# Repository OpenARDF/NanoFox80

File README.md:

# NanoFox80
NanoFox80 is a (relatively) simple full-featured low-power 80m transmitter for use in foxoring competitions.

<b>KiCad</b>

The KiCad folder holds files for generating the schematic, BOM, and PCB files using KiCad. 

<b>Software</b>

The Software folder holds files for compiling executable code on Atmel Studio 7.

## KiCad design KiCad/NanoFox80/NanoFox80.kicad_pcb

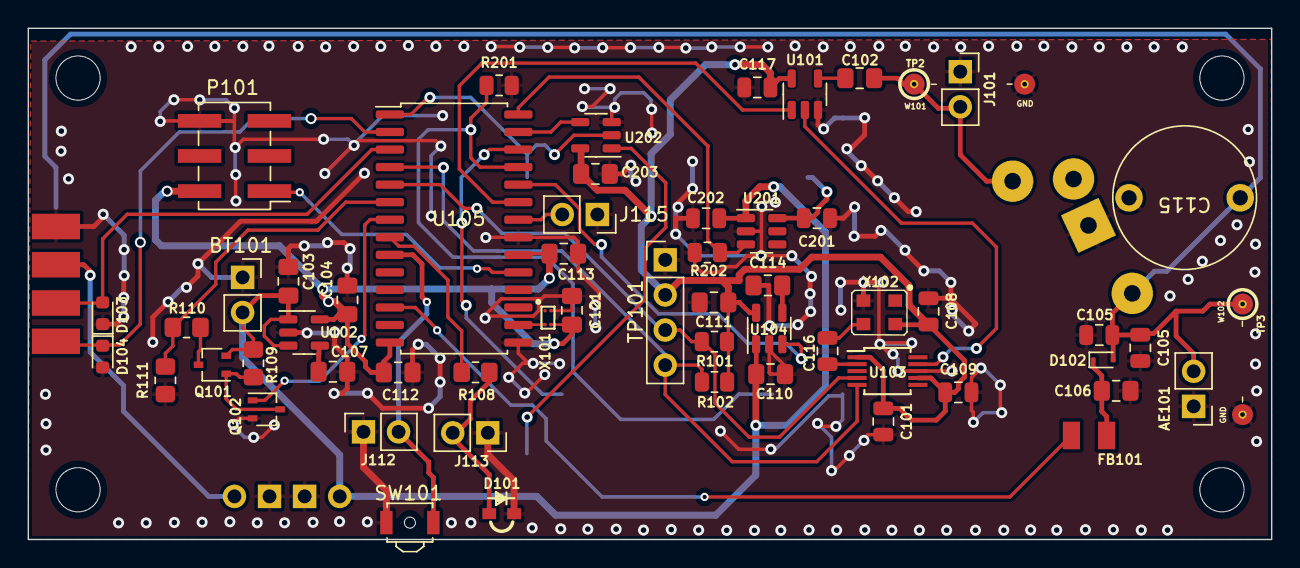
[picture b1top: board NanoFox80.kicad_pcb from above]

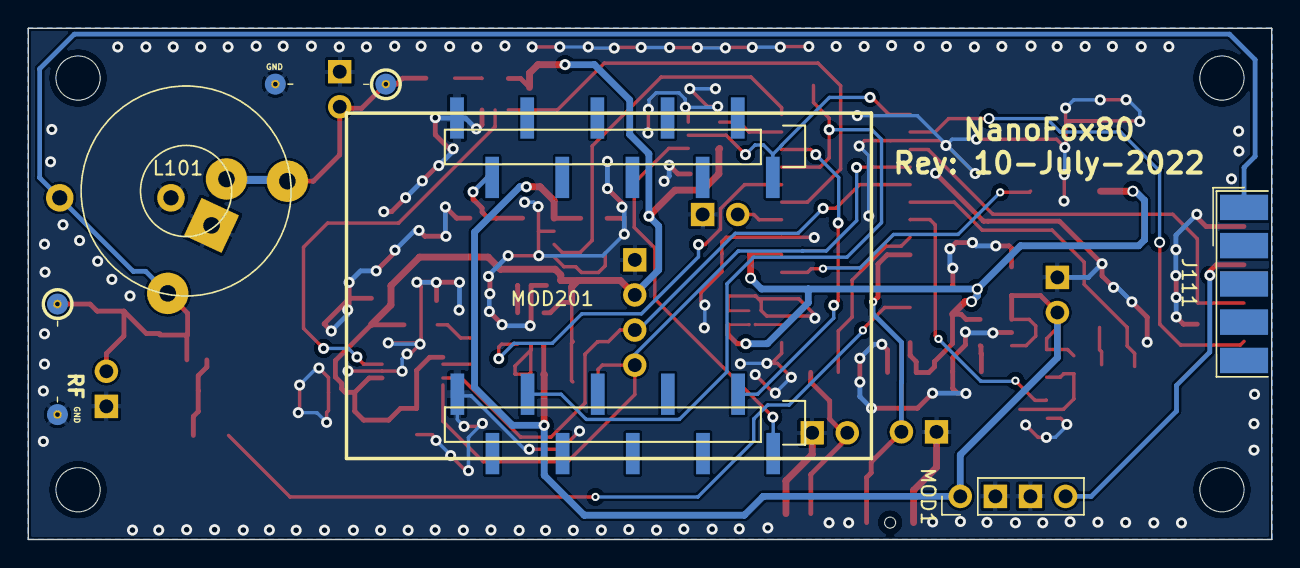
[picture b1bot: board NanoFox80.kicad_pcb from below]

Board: 2 copper layers, 90.0 x 37.0 mm, 61 parts (4 on the bottom side), 38 nets.

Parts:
AE101: Antenna_Shield; PinHeader_1x02_P2.54mm_Vertical
BT101: 3.5-9V; PinSocket_1x02_P2.54mm_Vertical
C101, C109: 470nF; C_0805_2012Metric
C102, C121, C203: 100nF; C_0805_2012Metric_Pad1.18x1.45mm_HandSolder
C103, C104, C110, C111: 10uF; C_0805_2012Metric_Pad1.18x1.45mm_HandSolder
C105, C105#2: 220pF; C_0805_2012Metric
C106, C112, C113: 470nF; C_0805_2012Metric_Pad1.18x1.45mm_HandSolder
C107, C114: 10nF; C_0805_2012Metric_Pad1.18x1.45mm_HandSolder
C108, C116, C117: 100nF; C_0805_2012Metric
C115: 15-60pF; CP_Radial_Ceramic_Trimmer_D9.4mm_P8.00mm
C201: 10uF; C_0805_2012Metric
C202: 4.7uF; C_0805_2012Metric
D101: LED_Filled; LED_APDA1806SECK
D102: SMV1253-079LF; D_SC-80
D103, D104: ESD9B5.0ST5G_1; D_0603_1608Metric
FB101: FerriteBead_Small; Ferrite_Bead_NFZ32BW881_Reflow
J101, J112, J113, J115: Conn_01x02; PinSocket_1x02_P2.54mm_Vertical
J111: DB9 Female; DSUB-9_Female_EdgeMount_P2.77mm
L101: 8uH; Autotransformer_Toroid_1Tap_Horizontal_D14.0mm_Amidon-T50
MOD1: AdaFruit Charger; PinHeader_1x04_P2.54mm_Vertical
MOD201: HUZZAH_ESP8266_Breakout; Adafruit_HUZZAH_ESP8266_Breakout_SM
P101: ISP/PDI; PinHeader_2x03_P2.54mm_Vertical_SMD
Q101: BSS84W-7-F; SOT-323_SC-70
Q102: BSS138W-7-F; SOT-323_SC-70
R101, R102, R202: 10k; R_0805_2012Metric
R108: 1k; R_0805_2012Metric_Pad1.20x1.40mm_HandSolder
R109: 100k; R_0805_2012Metric_Pad1.20x1.40mm_HandSolder
R110: 162k; R_0805_2012Metric_Pad1.20x1.40mm_HandSolder
R111: 12.4k; R_0805_2012Metric_Pad1.20x1.40mm_HandSolder
R201: 560k; R_0805_2012Metric
SW101: SW_SPST; SW_SPST_B3U-3000P-B
TP101: I2C1; PinHeader_1x04_P2.54mm_Vertical
U101: MC74VHC1G125; TSOT-23-5
U102, U104: LP2985-3.3; SOT-23-5
U103: SI5351; MSOP-10_3x3mm_P0.5mm
U105: AVR128DA28; SOIC-28W_7.5x17.9mm_P1.27mm
U201: TPS22810DBVT; SOT-23-6
U202: 74HC1G08; SOT-23-5
W101: TP2; Measurement_Point_ScopeProbe_Round-SMD-2sides-Pad_Small
W102: TP3; Measurement_Point_ScopeProbe_Round-SMD-2sides-Pad_Small
X101: SIT1566AC TCO; Oscillator_SMD_SiTime_SIT1566AC-4Pin_BGA
X102: 25 MHz; Crystal_SMD_TXETCLSANF-4Pin

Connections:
+3V3: C104.2, C112.1, C113.2, C121.2, P101.2, U102.5 (VOUT), U105.14 (AVDD), U105.20 (VDD), X101.3 (Vdd)
+BATT: BT101.2 (+), C103.2, C110.2, C202.2, MOD1.1, Q101.2 (S), R109.1, U102.1 (VIN), U102.3 (ON/~OFF), U104.1 (VIN), U201.1 (VIN)
Antenna: AE101.2 (A), C105.1, C105#2.1, C115.1, D102.2 (A), J111.1, L101.1, W102.1
Enable_RF: U104.3 (ON/~OFF), U105.24 (PA2)
Enable_Vdiv: Q102.1 (G), U105.7 (PD1)
GND: AE101.1 (Shield), BT101.1 (-), C101.2, C103.1, C104.1, C105.2, C105#2.2, C106.1, C107.2, C108.2, C109.2, C110.1, C111.1, C112.2, C113.1, C114.2, C115.2, C117.1, C121.1, C201.1, C202.1, C203.1, D101.1 (K), D103.1 (A1), D104.2 (A2), J101.1, J111.6, J112.1, J113.1, J115.1, L101.3, MOD1.2, MOD1.3, MOD201.10 (GND), MOD201.11 (GND), P101.6, Q102.2 (S), R111.1, R201.2, R202.1, SW101.2 (B), TP101.1, U101.3 (GND), U102.2 (GND), U103.8 (GND), U104.2 (GND), U105.15 (GND), U105.21 (GND), U201.2 (GND), U202.3 (GND), W101.2, W102.2, X101.4 (GND), X102.2 (GND)
unnamed: C102.1, J101.2, L101.2 (TAP), W101.1
unnamed: C102.2, U101.4 (Y)
unnamed: C106.2, D102.1 (K), FB101.1
unnamed: C107.1, U102.4 (BP)
unnamed: C114.1, U104.4 (BP)
unnamed: C116.1, U103.2 (XA)
unnamed: C116.2, X102.3 (OUT)
unnamed: C201.2, MOD201.9 (VBat), U201.6 (VOUT)
unnamed: D101.2 (A), J113.2, R108.2
unnamed: D103.2 (A2), J111.8, U105.3 (PC1/RxD1)
unnamed: D104.1 (A1), J111.9, U105.2 (PC0/TxD1)
unnamed: FB101.2, U105.12 (PD6/DAC)
unnamed: J112.2, SW101.1 (A), U105.9 (PD3)
unnamed: J115.2, U105.22 (PA0/EXTCLK)
unnamed: MOD201.20 (TX), U202.1
unnamed: P101.1, U105.19 (UDPI)
unnamed: Q101.1 (G), Q102.3 (D), R109.2
unnamed: Q101.3 (D), R110.2
unnamed: R101.2, TP101.3, U103.4 (SCL), U105.5 (PC3/SCL)
unnamed: R102.2, TP101.4, U103.5 (SDA), U105.4 (PC2/SDA)
unnamed: R108.1, U105.8 (PD2)
unnamed: U101.1 (~OE), U105.23 (PA1)
unnamed: U101.2 (A), U103.9 (CLK1)
unnamed: U105.16 (PF0/XTAL32k1), X101.2 (OUT)
V+_Charging: J111.7, MOD1.4
VCC: C101.1, C108.1, C109.1, C111.2, C117.2, C203.2, R101.1, R102.1, TP101.2, U101.5 (VCC), U103.1 (VDD), U103.7 (VDDO), U104.5 (VOUT), U202.5 (VCC), X102.4 (Vcc)
Vbat: R110.1, R111.2, U105.6 (PD0/AIN0)
WIFI_ENABLE: R202.2, U105.28 (PA6), U201.3 (EN/UVLO)
WIFI_RX: MOD201.19 (RX), U105.26 (PA4)
WIFI_TX: U105.27 (PA5), U202.4
WiFi Module Detect: MOD201.13 (3V), R201.1, U105.25 (PA3)
~WIFI_RESET: MOD201.1 (~RST), U105.1 (PA7), U202.2

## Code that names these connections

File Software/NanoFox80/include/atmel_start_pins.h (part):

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/**
 * \brief Set ENABLE_Vdiv input/sense configuration
 *
 * Enable/disable ENABLE_Vdiv digital input buffer and pin change interrupt,
 * select pin interrupt edge/level sensing mode
 *
 * \param[in] isc PORT_ISC_INTDISABLE_gc    = Iterrupt disabled but input buffer enabled
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}

/**
 * \brief Set PC0 pull mode
 *
 * Configure pin to pull up, down or disable pull mode, supported pull
 * modes are defined by device used
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}

/**
 * \brief Set PC0 data direction
 *
 * Select if the pin data direction is input, output or disabled.
 * If disabled state is not possible, this function throws an assert.
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}

/**
 * \brief Set PC0 input/sense configuration
 *
 * Enable/disable PC0 digital input buffer and pin change interrupt,
 * select pin interrupt edge/level sensing mode
 *
 * \param[in] isc PORT_ISC_INTDISABLE_gc    = Iterrupt disabled but input buffer enabled
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}

/**
 * \brief Set PC0 inverted mode
 *
 * Enable or disable inverted I/O on a pin
 *
 * \param[in] inverted true  = I/O on PC0 is inverted
 *                     false = I/O on PC0 is not inverted
 */
static inline void PC0_set_inverted(const bool inverted)
{
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}

/**
 * \brief Set PC0 level
 *
 * Sets output level on a pin
 *
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}

/**
 * \brief Toggle output level on PC0
 *
 * Toggle the pin level
 */
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}

/**
 * \brief Get level on PC0
 *
 * Reads the level on a pin
 */
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}

/**
 * \brief Set PC1 pull mode
 *
 * Configure pin to pull up, down or disable pull mode, supported pull
 * modes are defined by device used
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}

/**
 * \brief Set PC1 data direction
 *
 * Select if the pin data direction is input, output or disabled.
 * If disabled state is not possible, this function throws an assert.
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}

/**
 * \brief Set PC1 input/sense configuration
 *
 * Enable/disable PC1 digital input buffer and pin change interrupt,
 * select pin interrupt edge/level sensing mode
 *
 * \param[in] isc PORT_ISC_INTDISABLE_gc    = Iterrupt disabled but input buffer enabled
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}

/**
 * \brief Set PC1 inverted mode
 *
 * Enable or disable inverted I/O on a pin
 *
 * \param[in] inverted true  = I/O on PC1 is inverted
 *                     false = I/O on PC1 is not inverted
 */
static inline void PC1_set_inverted(const bool inverted)
{
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}

/**
 * \brief Set PC1 level
 *
 * Sets output level on a pin
 *
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}

/**
 * \brief Toggle output level on PC1
 *
 * Toggle the pin level
 */
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}

/**
 * \brief Get level on PC1
 *
 * Reads the level on a pin
 */
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}

/**
 * \brief Set PC2 pull mode
 *
 * Configure pin to pull up, down or disable pull mode, supported pull
 * modes are defined by device used
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}

/**
 * \brief Set PC2 data direction
 *
 * Select if the pin data direction is input, output or disabled.
 * If disabled state is not possible, this function throws an assert.
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}

/**
 * \brief Set PC2 input/sense configuration
 *
 * Enable/disable PC2 digital input buffer and pin change interrupt,
 * select pin interrupt edge/level sensing mode
 *
 * \param[in] isc PORT_ISC_INTDISABLE_gc    = Iterrupt disabled but input buffer enabled
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}

/**
 * \brief Set PC2 inverted mode
 *
 * Enable or disable inverted I/O on a pin
 *
 * \param[in] inverted true  = I/O on PC2 is inverted
 *                     false = I/O on PC2 is not inverted
 */
static inline void PC2_set_inverted(const bool inverted)
{
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}

/**
 * \brief Set PC2 level
 *
 * Sets output level on a pin
 *
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}

/**
 * \brief Toggle output level on PC2
 *
 * Toggle the pin level
 */
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}

/**
 * \brief Get level on PC2
 *
 * Reads the level on a pin
 */
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}

/**
 * \brief Set PC3 pull mode
 *
 * Configure pin to pull up, down or disable pull mode, supported pull
 * modes are defined by device used
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}

/**
 * \brief Set PC3 data direction
 *
 * Select if the pin data direction is input, output or disabled.
 * If disabled state is not possible, this function throws an assert.
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}

/**
 * \brief Set PC3 input/sense configuration
 *
 * Enable/disable PC3 digital input buffer and pin change interrupt,
 * select pin interrupt edge/level sensing mode
 *
 * \param[in] isc PORT_ISC_INTDISABLE_gc    = Iterrupt disabled but input buffer enabled
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}

/**
 * \brief Set PC3 inverted mode
 *
 * Enable or disable inverted I/O on a pin
 *
 * \param[in] inverted true  = I/O on PC3 is inverted
 *                     false = I/O on PC3 is not inverted
 */
static inline void PC3_set_inverted(const bool inverted)
{
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}

/**
 * \brief Set PC3 level
 *
 * Sets output level on a pin
 *
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}

/**
 * \brief Toggle output level on PC3
 *
 * Toggle the pin level
 */
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}

/**
 * \brief Get level on PC3
 *
 * Reads the level on a pin
 */
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}

/**
 * \brief Set PD0 pull mode
 *
 * Configure pin to pull up, down or disable pull mode, supported pull
 * modes are defined by device used
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}

/**
 * \brief Set PD0 data direction
 *
 * Select if the pin data direction is input, output or disabled.
 * If disabled state is not possible, this function throws an assert.
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}

/**
 * \brief Set PD0 input/sense configuration
 *
 * Enable/disable PD0 digital input buffer and pin change interrupt,
 * select pin interrupt edge/level sensing mode
 *
 * \param[in] isc PORT_ISC_INTDISABLE_gc    = Iterrupt disabled but input buffer enabled
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}

/**
 * \brief Set PD0 inverted mode
 *
 * Enable or disable inverted I/O on a pin
 *
 * \param[in] inverted true  = I/O on PD0 is inverted
 *                     false = I/O on PD0 is not inverted
 */
static inline void PD0_set_inverted(const bool inverted)
{
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}

/**
 * \brief Set PD0 level
 *
 * Sets output level on a pin
 *
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}

/**
 * \brief Toggle output level on PD0
 *
 * Toggle the pin level
 */
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}

/**
 * \brief Get level on PD0
 *
 * Reads the level on a pin
 */
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}

/**
 * \brief Set PD6 pull mode
 *
 * Configure pin to pull up, down or disable pull mode, supported pull
 * modes are defined by device used
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}

/**
 * \brief Set PD6 data direction
 *
 * Select if the pin data direction is input, output or disabled.
 * If disabled state is not possible, this function throws an assert.
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}

/**
 * \brief Set PD6 input/sense configuration
 *
 * Enable/disable PD6 digital input buffer and pin change interrupt,
 * select pin interrupt edge/level sensing mode
 *
 * \param[in] isc PORT_ISC_INTDISABLE_gc    = Iterrupt disabled but input buffer enabled
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}

/**
 * \brief Set PD6 inverted mode
 *
 * Enable or disable inverted I/O on a pin
 *
 * \param[in] inverted true  = I/O on PD6 is inverted
 *                     false = I/O on PD6 is not inverted
 */
static inline void PD6_set_inverted(const bool inverted)
{
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}

/**
 * \brief Set PD6 level
 *
 * Sets output level on a pin
 *
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}

/**
 * \brief Toggle output level on PD6
 *
 * Toggle the pin level
 */
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}

/**
 * \brief Get level on PD6
 *
 * Reads the level on a pin
 */
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
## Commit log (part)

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2022-04-22 First Commit
    Adds KiCad files
2022-04-22 Removed backup files
2022-04-23 Schematic Updates
    o Specified missing part parameters
    o Added Q101 & Q102, R110, R111, to support battery voltage monitoring
    o Added JP104 and JP105 to support swapping inputs to
2022-04-23 Cleanup
2022-04-25 Added test points
    Added photos in Docs folder
    Added test points
2022-04-26 Updates
    o More parts specified
    o First cut at a PCB
2022-04-26 Schematic Update
    o Added ESD diodes
2022-04-26 Parts Update
    Changed LED to be a right-angle device
2022-04-26 BOM
    o Fixed BOM script
    o Generated preliminary BOM
2022-04-27 Updated Schematic & PCB
    o Corrected varactor circuit
    o Added level translation to USART
    o Added mounting holes to PCB
2022-04-28 Schematic Update
    Updated L101 information
2022-04-30 PCB Routed
    o First cut at PCB board
    o Gerbers updated
2022-04-30 PCB Updates
    o Added better silkscreen to X101
    o More stitch vias
2022-05-01 PCB Updates
    o Added holes for scope probe ground clips
2022-05-01 PCB Update
    Updated X101 footprint silkscreen
2022-05-02 Schematic & PCB updates
    o Moved X101 connection to U105
    o Added header to pin 22 of U105
    o Updated schematic and PCB
    o Generated new Gerbers
2022-05-03 Updated Footprints
    o Corrected U106, U107 and U103 footprints
    o Updated Gerbers
2022-05-04 Schematic & PCB Updates
    o Fixed pinout of Q101
    o Changed device for U103
    o Corrected PCB for Q101 change
    o Updated PCB Rev
    o Updated BOM
2022-05-04 Schematic, BOM and PCB Updates
    o Changed parts spec'd for Q101 and Q102
    o Updated footprints
    o Updated PCB
    o Updated Gerbers
    o Updated BOM
2022-05-05 PCB Update
    o Corrected footprint for U103
    o Updated Gerbers
    o Updated BOM
2022-05-05 Moved Gerbers
    o Added a folder to hold all the Gerber files
2022-06-29 Last PLL Changes
    Merge last development changes supporting the PLL concept design
2022-06-29 Development for Si5351
    First changes for Si5351 design approach
2022-06-30 Development
    o Schematic updates for Si5351 approach
2022-06-30 Development
    o Addressed ERC errors
    o Added trimmer capacitor
    o Cosmetic changes to schematic
2022-06-30 Development
    o Added ESD diodes
    o Added WiFi support
2022-06-30 Development
    o Added last Microchip Studio files developed for the PLL design
2022-06-30 Development
    o Added Software folder
2022-07-01 Development
    o Set all footprints to approximate values
2022-07-01 Development
    Updated .gitignore
2022-07-02 Development
    o Added initial software folder
2022-07-02 Development
    o Removed zip files
2022-07-02 Development
    o Changes to footprints in schematic
2022-07-03 Development
    o Initialize PA7 correctly
2022-07-03 Development
    o Minor cleanup
2022-07-04 Development
    o Footprint edits
2022-07-04 Development
    o Tweak X102 footprint on PCB
2022-07-06 Development
    o Fixes to errors in schematic and PCB
2022-07-10 Development
    PCB changes
2022-07-10 Development
    Small PCB tweaks
2022-07-11 Development
    PCB silkscreen change
2022-07-12 PCB Dev
    o Removed copper fill keep out zone beneath X101
2022-07-12 Built Gerbers
    o Uploading built Gerber files
2022-07-12 PCB Development
    Tweaks to X101 footprint
2022-08-06 Development Merge
    o Merge of FlexFox software ported to NanoFox hardware. Little debugging has been done at this point.
2022-08-07 Development
    Debug of power to SI5351.
2022-08-07 Development
    o Implemented a DAC setting command for the serial bus.
    o Removed the power-setting command from the serial bus.
2022-08-08 Schematic Update
    o Updated L101 info
2022-08-08 Development
    o Timed events are now partly working
2022-08-09 Debug
    o Corrected a potential infinite loop if the TCXO hardware fails
2022-08-09 Development
    o Fixed some LED blink issues
2022-08-09 Development
    Changes to SLP
    Version 0.42
2022-08-09 Development
    o Added SLP functionality: SLP 0 disables sleep; SLP 1 re-enables sleep; SLP starts sleep if it isn't enabled
    o Fixes a bug that prevented ADC from working after returning from sleep
    o Ver 0.43
2022-08-09 Development
    o The sleep countdown is now reset to 2 minutes every time a serial port command is sent to NanoFox.
    o Ver 0.44
2022-08-09 Development
    o Improved sleep current drain. Now down to 336 uA.
    o Ver 0.45
2022-08-09 Schematic Updates
    o Corrected the device symbol for the microcontroller.
2022-08-10 Development
    o Fixes several problems that prevented the RTC from incrementing during sleep when using the internal 32 kHz clock.
2022-08-11 Development
    o Fix for Morse code timing that could send extra elements after sending the station ID
    o EEPROM variables added for future support of setting foxoring event information
2022-08-12 Development
    o Ver 0.50
    o Added non-volatile variables and commands to support "Event" concept and master/slave synchronization
2022-08-13 Ver 0.51
    o Added code to test the cloning concept. It should successfully set a slave's clock.
    o Added support for enunciating with Morse LED blinks
    o Removed Goertzel algorithm
2022-08-15 Development
    o Fixes an issue preventing time from getting sync'd during cloning process
    o Master will never transmit now
    o 1 short buttonpress should start an event
    o 2 short buttonpresses should stop an event
    o Ver 0.52
2022-08-15 Development
    o Ver 0.52
2022-08-15 Development
    Ver 0.52
2022-08-16 Development
    Ver 0.53
    o Fixes to cloning process
2022-08-16 Development
    Ver 0.54
    o Corrects a problem with Master/Slave sending \n instead of \r.
    o Addresses an issue that might have been corrupting g_foxoring_fox
2022-08-16 Development
    Prevents a slave from recognizing MAS P<cr> command for one minute following a successful cloning session.
2022-08-16 Ver 0.56
    o Removed echoing of characters during cloning.
2022-08-16 Ver 0.57
    Removed more extraneous character traffic during cloning.
2022-08-17 Ver 0.58
    o Sync debug
2022-08-17 Ver 0.59
    o Corrects an issue where master would send the start time in the CLK F message
2022-08-17 Development
    o Slave LED illuminates continuously while cloning is taking place.
    o Long keypress no longer sends "Master" or "Slave" after a mode transition.
2022-08-21 Ver 0.6
    o Added BAT serial command to display battery voltage and threshold setting.
    o Added a battery threshold setting that sets at what voltage the LED blinks "V" to indicate low battery. By default it is 3.8V.
    o Added a checksum for cloning data, and a master/slave message exchange to implement serial data error detection.
    o Code cleanup and general bug fixes.
2022-08-22 Ver 0.61
    o Redesign of EEPROM module. Guard variables added between settings variables.
    o Corrects some problems with event behavior following a sync
    o Corrects some problems with event behavior when going between master and slave mode or changing fox setting.
2022-08-23 KiCad
    o Schematic updates
2022-08-29 Ver 0.62
    o Adds support for RTC calibration using the CLK C nnnnn serial command.
    o Cleans up some EEPROM design elements
    o Minor bug fixes.
2022-09-01 Ver 0.63
    o Corrects a bug that could prevent the finish time from getting saved when the CLK S serial command was used to set the start time.
2022-11-21 +BATT Fix
    Schematic change
2022-11-21 Update NanoFox80.kicad_sch
    Schematic tweaks.
2022-11-21 Update NanoFox80.kicad_sch
    More tweaks
2022-11-21 Update NanoFox80.kicad_sch
    Schematic tweak - added cap across switch
2022-11-22 Schematic Tweaks
    Added missing diode
2022-11-22 Update NanoFox80.kicad_sch
    Schematic tweaks
2022-11-22 Schematic
    Upped version number
2022-11-23 Ver 0.64
    o Improved pushbutton debounce
2023-05-19 Fixed for EEPROM Corruption?
    Made changes to serial port logic to remove most junk characters.
    Set Port C Rx and Tx pins high during sleep.
    Disabled the linkbus, which isn't supported right now
2023-05-28 Development
    Adding support for all radio orienteering events formats
2023-05-30 Development Ver 0.71
    Numerous fixes to serial port operation.
2023-06-02 Serial Port Change
    o When device goes to sleep only two things will re-enable the serial port: 1) cycle power, 2) press button
    o Ver 0.72
2023-06-03 Bug Fix
    Resolves a bug that prevented the foxoring pattern code speed from getting set.
2023-06-03 Bug Fix
    Fixes a problem that prevented successful cloning
2023-06-04 Bug Fix
    Corrects a problem in which a master would never go to sleep after having completed a cloning session.
2023-06-05 Bug Fixes
    Should fix several issues that prevented sleep from occurring.
2023-06-05 Sleep Bug Fixes
    More fixes to sleep operation. Ver 0.77
2023-06-05 Debugging
    o Corrects a problem during sync in which the cloned frequencies do not get saved to the slave.
    o Corrects a problem in which a single button press will not cause a scheduled event to start immediately.
2023-06-06 Bugfix
    Corrects a very tricky issue with Port A Pin 1 when the linkbus is left enabled.
2023-06-29 Minor Bug Fix
    Add <CR> to BAT command response
2023-07-02 Runs Daily
    o Added support for running every day at the same time interval
    o Corrected a bug related to EEPROM storage
    o Corrected a bug related to using the GO 2 command
2023-07-04 Ver 0.83
    o Removed legacy code for linkbus and Huzzah module
    o Disabled DAC
    o Fixes bugs related to serial port
    o Sleep current is now 250uA
2023-07-12 Ver 0.84
    o Changed multi-day event setting CLK D to set the number of days to run, instead of running forever
    o Minor bug fixes
2023-07-13 Ver 0.85
    o Merged second-edge timing from FlexFox to NanoFox. Over/underlap between cycling transmitters is now unnoticeable.
2023-07-19 Ver 0.86
    o Synchronize clocks to seconds transition when syncing clocks to improve precision of synchronization
    o Minor bug fixes
2023-07-19 Ver 0.87
    o Corrects a bug that could cause the sleep time to be too short after an event is suspended.
2023-07-20 Ver 0.88
    o Fixes a situation that could result in the LED being left on continuously for an indefinite period of time.
2023-07-22 Ver 0.89
    o Corrects a bug that could result in a synced device not starting a programmed event.
2023-07-28 Ver 0.91
    o Updated toolchain. New zip file included with extension "update"
    o Fixes some sleep issues
    o Fixes some minor syntax errors
2023-07-29 Ver 0.92
    o Added VER serial test command to retrieve SW version
    o Fixes some EEPROM variable size issues that might result in data corruption
    o Fixes minor bug issues
2023-07-29 Ver 0.93
    Corrects a problem that could result in the wrong pattern code speed being sent.
2023-07-30 Ver 0.94
    o Bug fixes related to sleep and event startup
2023-07-30 Ver 0.95
    Corrects a problem that prevented entering Master Mode if an event is running.
2023-07-30 Ver 0.96
    Corrects a problem where the LED could start blinking garbage after returning from Master setting.
2023-07-31 Ver 0.97
    o Corrects several bugs related to pushbutton operation
    o Corrects a bug that could cause Morse characters to be sent by the LED after returning from sleep
2023-07-31 Ver 0.98
    o Corrects a bug that can cause the LED to blink Morse patterns when it should not.
2023-09-12 Debug
    o Fixes an issue with the "Days" feature that could cause a 1-day event to repeat.
    o Adds an I2C error counter and a DBG command to read it
2023-10-09 Bugfix & Debug
    o Adds I2C debug support
    o Fixes issue causing Master not to blink LED
2024-01-05 Keypress Improvements
    o Updates keypress detection to support up to 5 button presses.
    o LED blink improvements
2024-01-05 UI Improvemenyt
    o Distinguishes between ? command and a CR.
